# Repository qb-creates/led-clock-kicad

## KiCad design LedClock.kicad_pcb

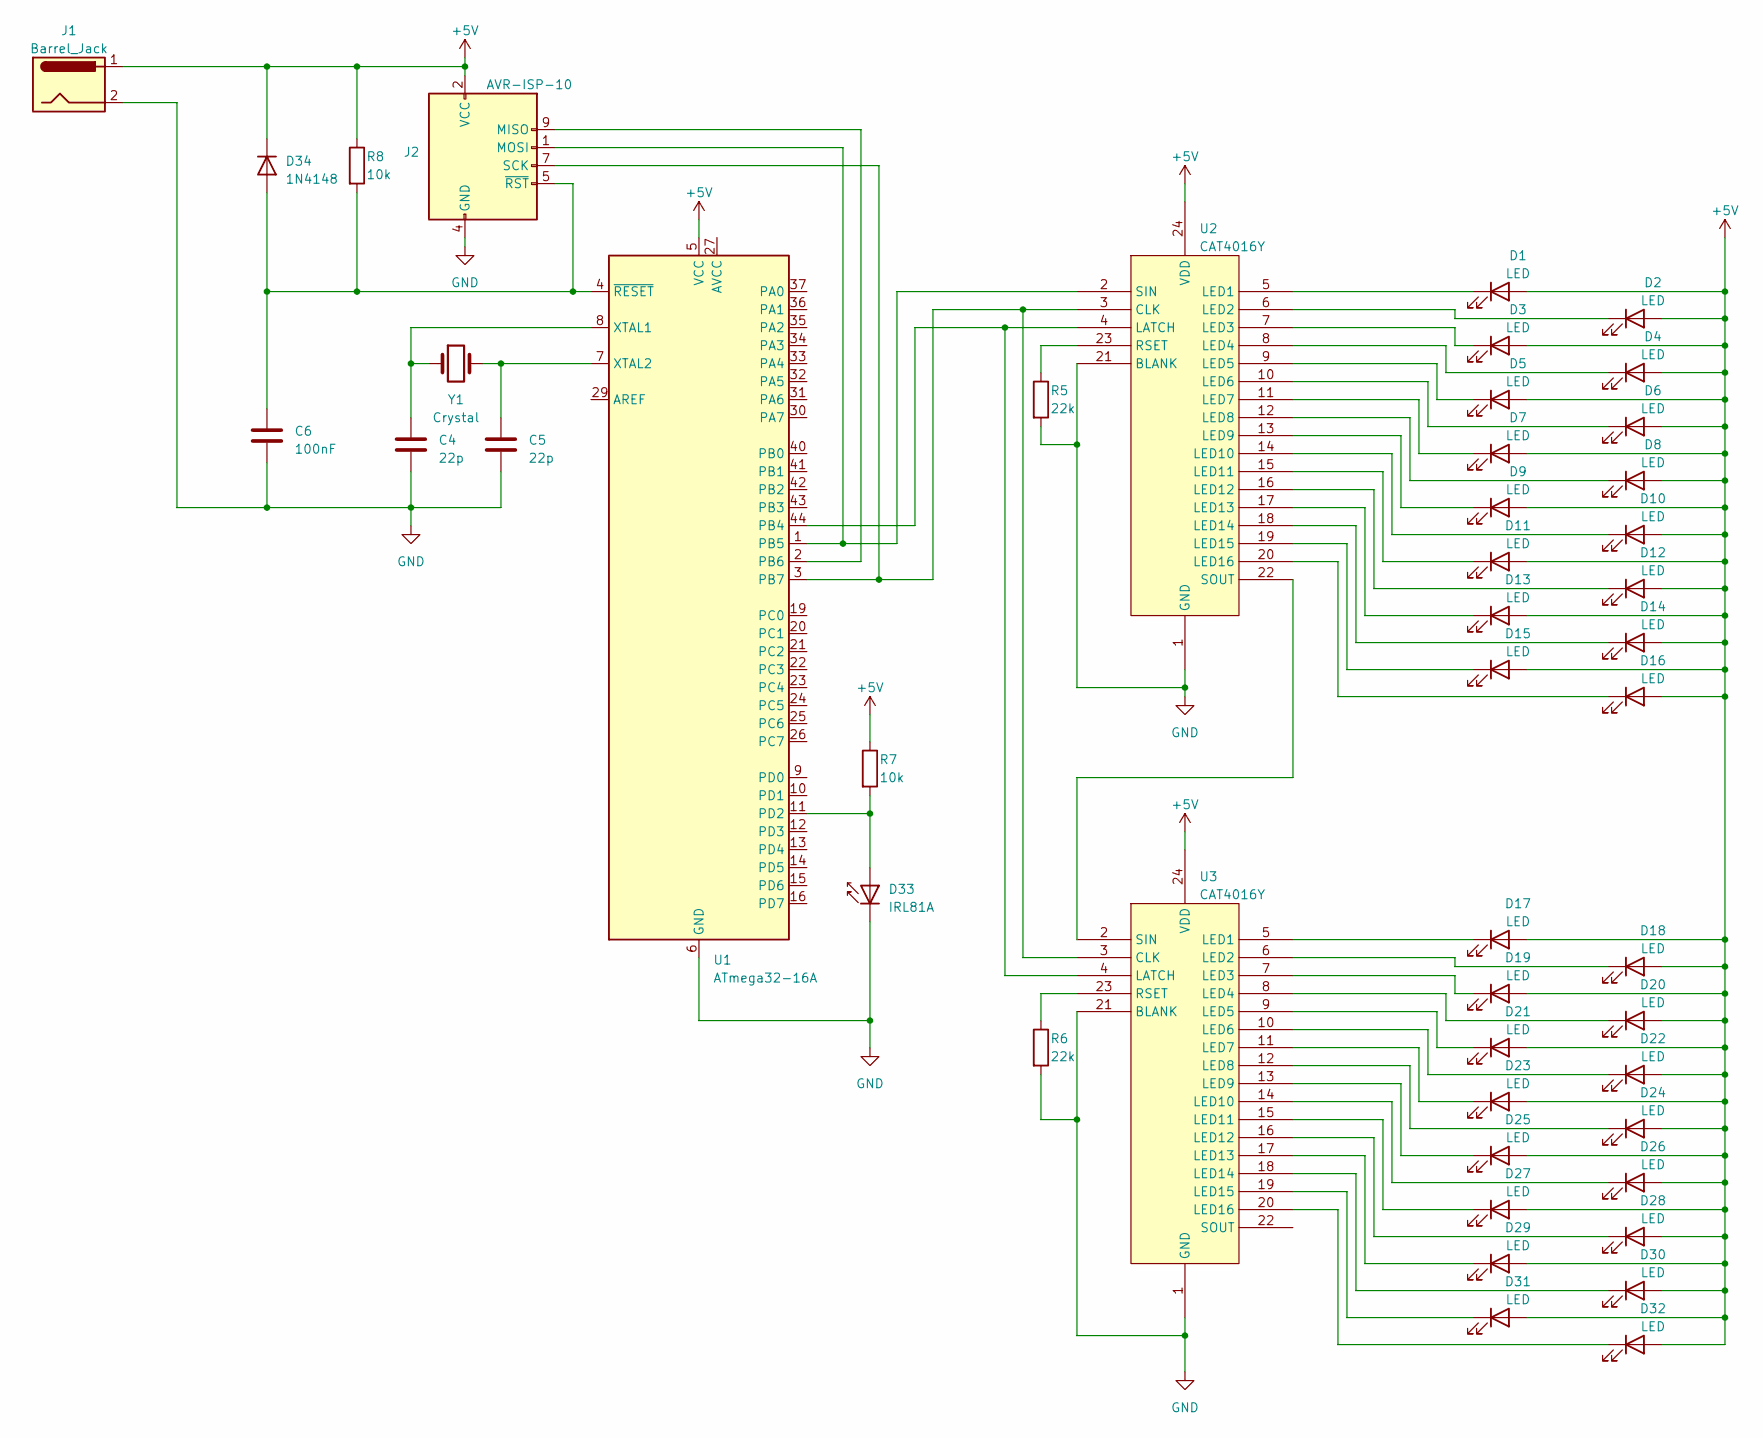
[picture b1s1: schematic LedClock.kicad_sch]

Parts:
C4, C5: 22p; C_0201_0603Metric_Pad0.64x0.40mm_HandSolder
C6: 100nF; C_0201_0603Metric_Pad0.64x0.40mm_HandSolder
D1, D2, D3, D4, D5, D6, D7, D8, D9, D10, D11, D12, D13, D14, D15, D16, D17, D18, D19, D20, D21, D22, D23, D24, D25, D26, D27, D28, D29, D30, D31, D32: LED; LED_1206_3216Metric
D33: IRL81A; LED_SideEmitter_Rectangular_W4.5mm_H1.6mm
D34: 1N4148; D_DO-35_SOD27_P7.62mm_Horizontal
J1: Barrel_Jack; JST_PH_S2B-PH-SM4-TB_1x02-1MP_P2.00mm_Horizontal
J2: AVR-ISP-10; ISP-10
R5, R6: 22k; R_0201_0603Metric_Pad0.64x0.40mm_HandSolder
R7, R8: 10k; R_0201_0603Metric_Pad0.64x0.40mm_HandSolder
U1: ATmega32-16A; TQFP-44_10x10mm_P0.8mm
U2, U3: CAT4016Y; SOIC-24W_7.5x15.4mm_P1.27mm
Y1: Crystal; Crystal_HC49-4H_Vertical

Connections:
+5V: D1.2 (A), D2.2 (A), D3.2 (A), D4.2 (A), D5.2 (A), D6.2 (A), D7.2 (A), D8.2 (A), D9.2 (A), D10.2 (A), D11.2 (A), D12.2 (A), D13.2 (A), D14.2 (A), D15.2 (A), D16.2 (A), D17.2 (A), D18.2 (A), D19.2 (A), D20.2 (A), D21.2 (A), D22.2 (A), D23.2 (A), D24.2 (A), D25.2 (A), D26.2 (A), D27.2 (A), D28.2 (A), D29.2 (A), D30.2 (A), D31.2 (A), D32.2 (A), D34.1 (K), J1.1, J2.2 (VCC), R7.1, R8.1, U1.5 (VCC), U1.17 (VCC), U1.38 (VCC), U2.24 (VDD), U3.24 (VDD)
GND: C4.2, C5.2, C6.2, D33.1 (K), J1.2, J2.4 (GND), J2.6 (GND), J2.8 (GND), J2.10 (GND), R5.2, R6.2, U1.6 (GND), U1.18 (GND), U1.28 (GND), U1.39 (GND), U2.1 (GND), U2.21 (BLANK), U3.1 (GND), U3.21 (BLANK)
unnamed: D1.1 (K), U2.5 (LED1)
unnamed: D2.1 (K), U2.6 (LED2)
unnamed: D3.1 (K), U2.7 (LED3)
unnamed: D4.1 (K), U2.8 (LED4)
unnamed: D5.1 (K), U2.9 (LED5)
unnamed: D6.1 (K), U2.10 (LED6)
unnamed: D7.1 (K), U2.11 (LED7)
unnamed: D8.1 (K), U2.12 (LED8)
unnamed: D9.1 (K), U2.13 (LED9)
unnamed: D10.1 (K), U2.14 (LED10)
unnamed: D11.1 (K), U2.15 (LED11)
unnamed: D12.1 (K), U2.16 (LED12)
unnamed: D13.1 (K), U2.17 (LED13)
unnamed: D14.1 (K), U2.18 (LED14)
unnamed: D15.1 (K), U2.19 (LED15)
unnamed: D16.1 (K), U2.20 (LED16)
unnamed: D17.1 (K), U3.5 (LED1)
unnamed: D18.1 (K), U3.6 (LED2)
unnamed: D19.1 (K), U3.7 (LED3)
unnamed: D20.1 (K), U3.8 (LED4)
unnamed: D21.1 (K), U3.9 (LED5)
unnamed: D22.1 (K), U3.10 (LED6)
unnamed: D23.1 (K), U3.11 (LED7)
unnamed: D24.1 (K), U3.12 (LED8)
unnamed: D25.1 (K), U3.13 (LED9)
unnamed: D26.1 (K), U3.14 (LED10)
unnamed: D27.1 (K), U3.15 (LED11)
unnamed: D28.1 (K), U3.16 (LED12)
unnamed: D29.1 (K), U3.17 (LED13)
unnamed: D30.1 (K), U3.18 (LED14)
unnamed: D31.1 (K), U3.19 (LED15)
unnamed: D32.1 (K), U3.20 (LED16)
unnamed: D33.2 (A), R7.2, U1.11 (PD2)
unnamed: C6.1, D34.2 (A), J2.5 (~RST), R8.2, U1.4 (~RESET)
unnamed: J2.9 (MISO), U1.2 (PB6)
unnamed: J2.1 (MOSI), U1.1 (PB5), U2.2 (SIN)
unnamed: J2.7 (SCK), U1.3 (PB7), U2.3 (CLK), U3.3 (CLK)
unnamed: U1.44 (PB4), U2.4 (LATCH), U3.4 (LATCH)
unnamed: C4.1, U1.8 (XTAL1), Y1.1
unnamed: C5.1, U1.7 (XTAL2), Y1.2
unnamed: R5.1, U2.23 (RSET)
unnamed: U2.22 (SOUT), U3.2 (SIN)
unnamed: R6.1, U3.23 (RSET)

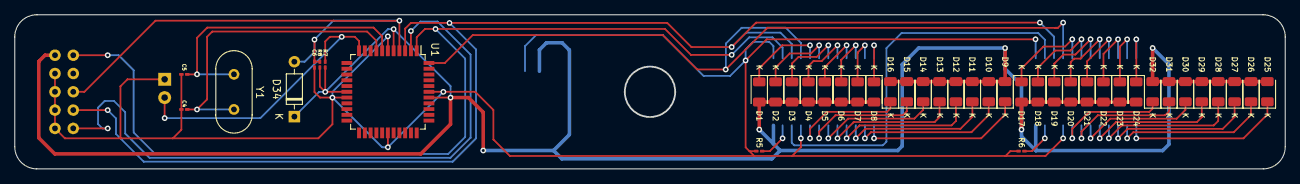
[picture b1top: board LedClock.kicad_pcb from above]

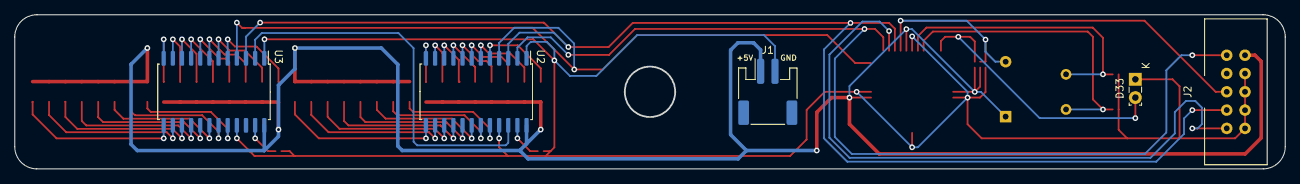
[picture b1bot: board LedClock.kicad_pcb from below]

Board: 2 copper layers, 176.4 x 21.4 mm, 47 parts (5 on the bottom side), 45 nets.

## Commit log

2023-03-10 Uploading the Project
